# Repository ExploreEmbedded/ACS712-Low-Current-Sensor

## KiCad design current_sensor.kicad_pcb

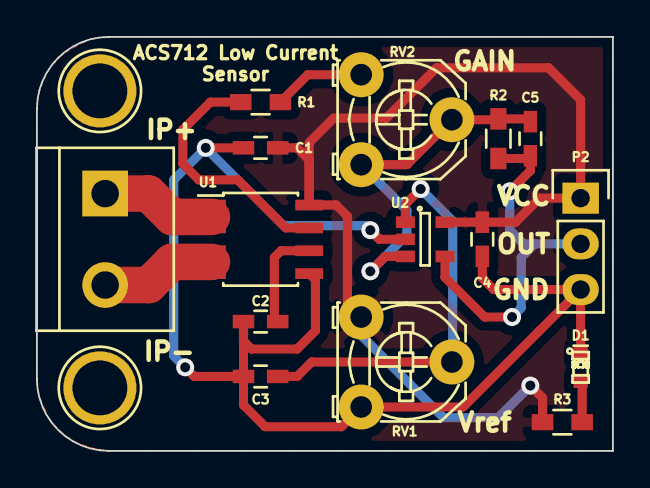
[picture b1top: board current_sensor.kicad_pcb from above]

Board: 2 copper layers, 32.0 x 23.0 mm, 18 parts (1 on the bottom side), 11 nets.

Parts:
C1, C3, C4, C5: 0.1uF; C_0603_HandSoldering
C2: 1nF; C_0603_HandSoldering
D1: LED; LED-0603_NEW
LOGO: LOGO (2)
P1: CONN_01X02; bornier2
P2: CONN_01X03; Pin_Header_Straight_1x03
P3, P4: CONN_01X01; 1pin
R1, R3: 1K; R_0603_HandSoldering
R2: 47K; R_0603_HandSoldering
RV1, RV2: POT; Potentiometer_Triwood_RM-065
U1: ACS712; SOIC-8_3.9x4.9mm_Pitch1.27mm
U2: LM_321; SOT-23-5

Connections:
GND: C1.2, C2.1, C3.1, C4.1, D1.2, P2.3, RV1.3, U1.5, U2.2
unnamed: C2.2, U1.6
unnamed: C3.2, RV1.2, U2.1
unnamed: C5.1, P2.2, R2.1, U2.4
unnamed: C5.2, R2.2, RV2.2, RV2.3, U2.3
unnamed: D1.1, R3.1
unnamed: P1.1, U1.1, U1.2
unnamed: P1.2, U1.3, U1.4
unnamed: R1.1, RV2.1
unnamed: R1.2, U1.7
VCC: C1.1, C4.2, P2.1, R3.2, RV1.1, U1.8, U2.5

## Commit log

2015-09-29 Added Files
2015-10-27 Added changed files
2015-10-27 changed legend
